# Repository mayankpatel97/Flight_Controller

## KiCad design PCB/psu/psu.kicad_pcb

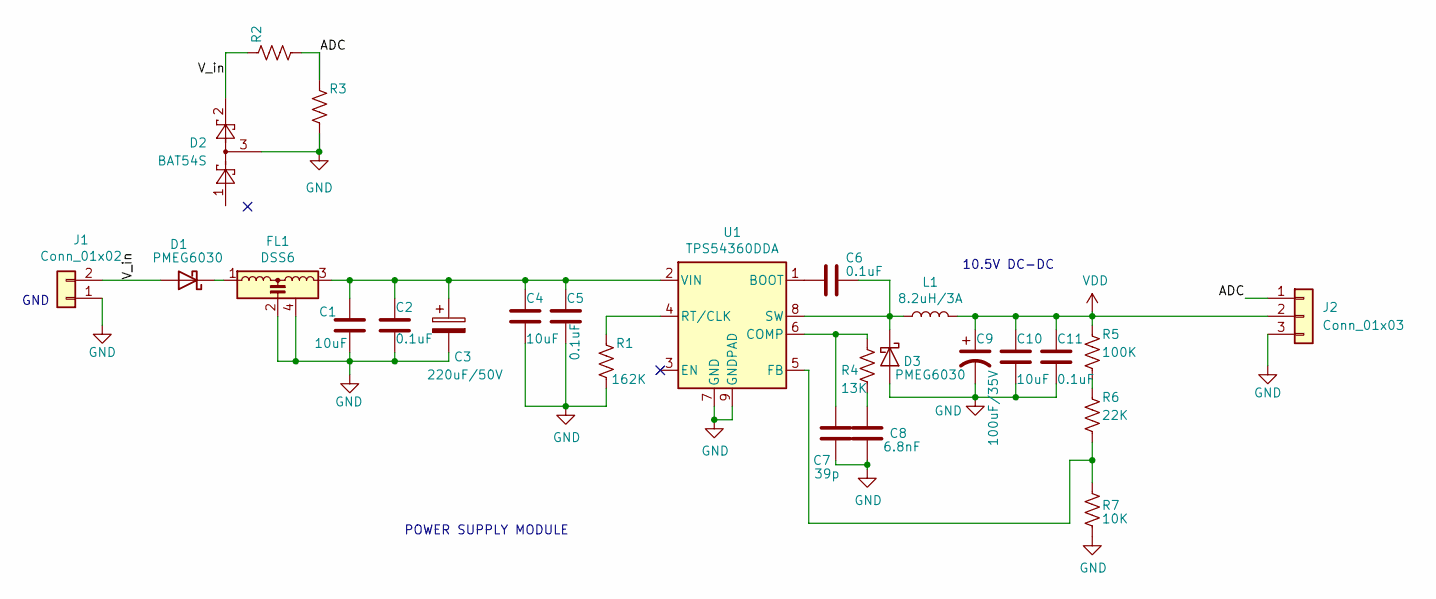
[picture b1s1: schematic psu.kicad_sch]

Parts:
C1, C4, C10: 10uF; C_0805_2012Metric_Pad1.18x1.45mm_HandSolder
C2, C5, C6, C11: 0.1uF; C_0805_2012Metric_Pad1.18x1.45mm_HandSolder
C3: 220uF/50V; CP_Elec_10x14.3
C7: 39p; C_0805_2012Metric_Pad1.18x1.45mm_HandSolder
C8: 6.8nF; C_0805_2012Metric_Pad1.18x1.45mm_HandSolder
C9: 100uF/35V; CP_Elec_10x14.3
D1, D3: PMEG6030; D_SMA
D2: BAT54S; SOT-23
FL1: DSS6; EMI_Filter_NFM41CC102R2A3L
J1: Conn_01x02; JST_XH_B2B-XH-A_1x02_P2.50mm_Vertical
J2: Conn_01x03; JST_EH_B3B-EH-A_1x03_P2.50mm_Vertical
L1: 8.2uH/3A; L_Neosid_Ms85
R1: 162K; R_0805_2012Metric_Pad1.20x1.40mm_HandSolder
R2, R3: 0; R_0805_2012Metric_Pad1.20x1.40mm_HandSolder
R4: 13K; R_0805_2012Metric_Pad1.20x1.40mm_HandSolder
R5: 100K; R_0805_2012Metric_Pad1.20x1.40mm_HandSolder
R6: 22K; R_0805_2012Metric_Pad1.20x1.40mm_HandSolder
R7: 10K; R_0805_2012Metric_Pad1.20x1.40mm_HandSolder
U1: TPS54360DDA; SOIC-8-1EP_3.9x4.9mm_P1.27mm_EP2.514x3.2mm_ThermalVias

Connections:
/ADC: J2.1, R2.2, R3.1
/V_in: D1.2 (A), D2.2, J1.2, R2.1
GND: C1.2, C2.2, C3.2, C4.2, C5.2, C7.1, C8.1, C9.2, C10.2, C11.2, D2.3, D3.2 (A), FL1.2, FL1.4 (GND), J1.1, J2.3, R1.2, R3.2, R7.2, U1.7 (GND), U1.9 (GNDPAD)
unnamed: C1.1, C2.1, C3.1, C4.1, C5.1, FL1.3, U1.2 (VIN)
unnamed: C6.1, D3.1 (K), L1.1, U1.8 (SW)
unnamed: C6.2, U1.1 (BOOT)
unnamed: C7.2, R4.1, U1.6 (COMP)
unnamed: C8.2, R4.2
unnamed: D1.1 (K), FL1.1
unnamed: R1.1, U1.4 (RT/CLK)
unnamed: R5.2, R6.1
unnamed: R6.2, R7.1, U1.5 (FB)
VDD: C9.1, C10.1, C11.1, J2.2, L1.2, R5.1

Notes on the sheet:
10.5V DC-DC
POWER SUPPLY MODULE
GND

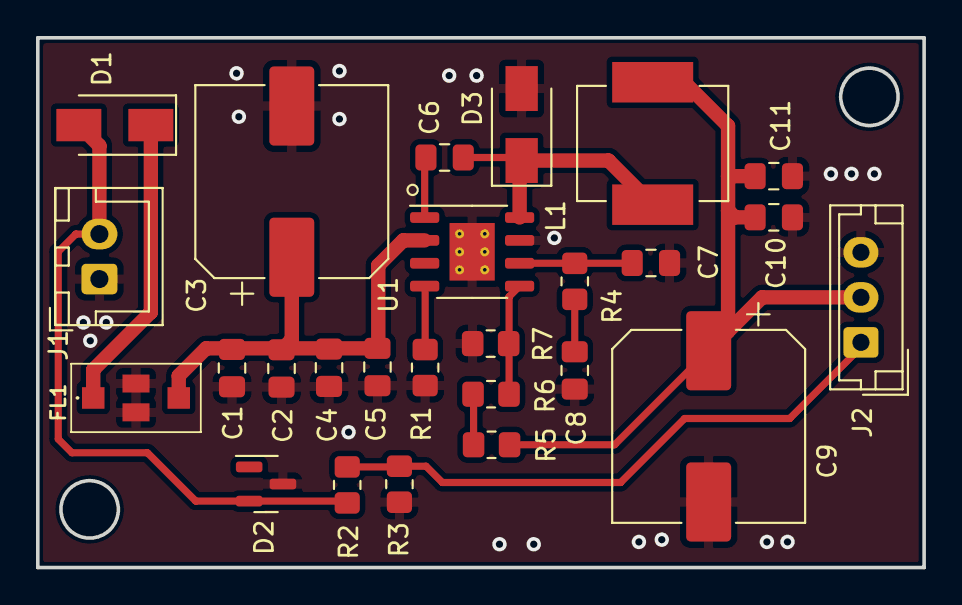
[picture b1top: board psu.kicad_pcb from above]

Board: 2 copper layers, 49.2 x 29.4 mm, 26 parts (0 on the bottom side), 13 nets.

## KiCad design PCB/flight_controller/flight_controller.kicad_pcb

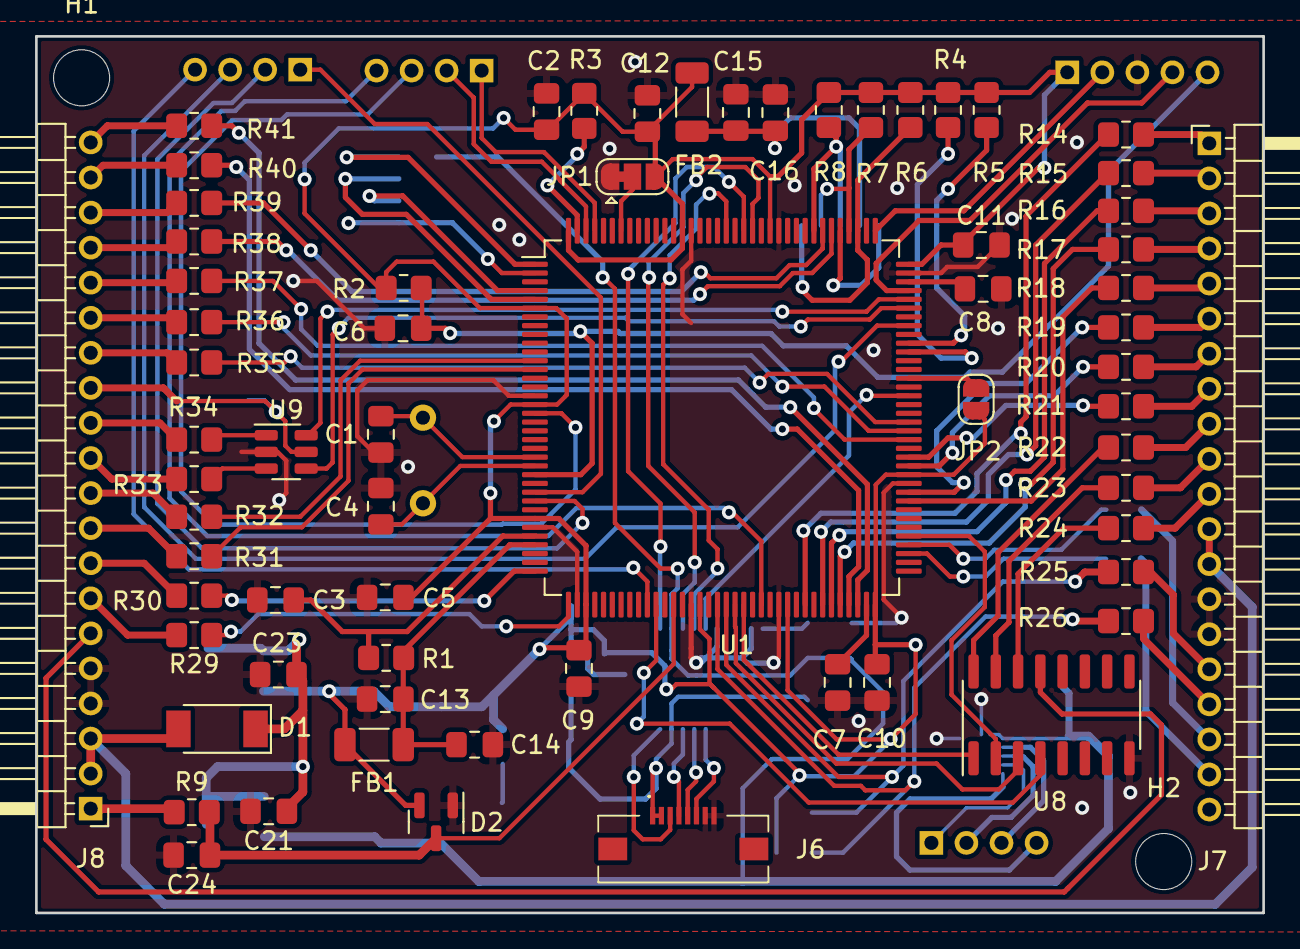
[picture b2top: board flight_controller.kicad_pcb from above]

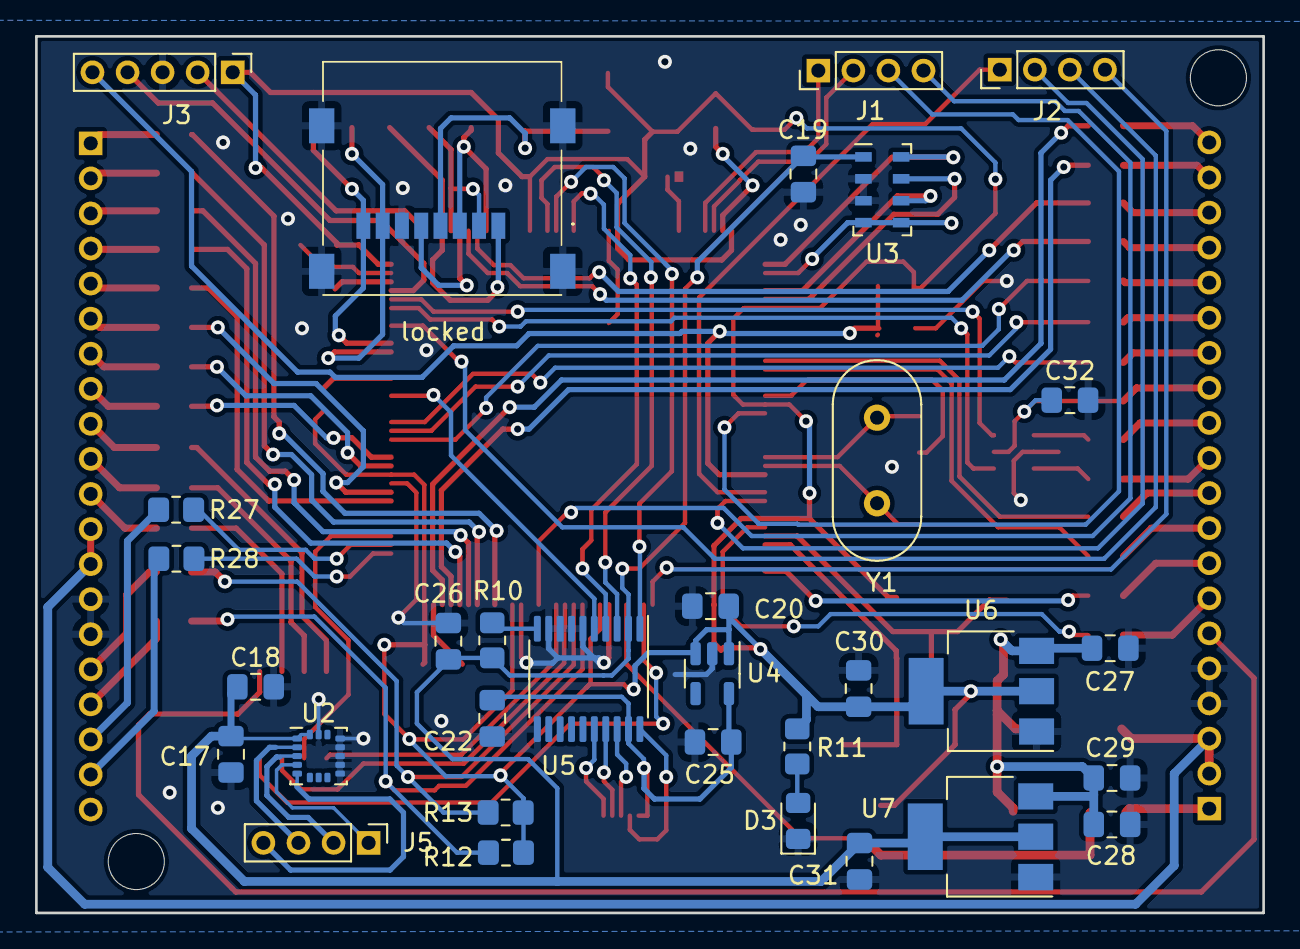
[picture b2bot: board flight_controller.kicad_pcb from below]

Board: 2 copper layers, 70.0 x 50.0 mm, 100 parts (32 on the bottom side), 117 nets.

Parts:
C1, C4: 27pF; C_0805_2012Metric_Pad1.18x1.45mm_HandSolder
C2, C5, C6, C9, C10, C11, C12, C13, C16, C17, C18, C19, C20, C22, C25, C26, C27, C29, C30, C31, C32: 0.1uF; C_0805_2012Metric_Pad1.18x1.45mm_HandSolder
C3, C7, C8, C14, C24: 1uF; C_0805_2012Metric_Pad1.18x1.45mm_HandSolder
C15, C21, C23: 22uF; C_0805_2012Metric_Pad1.18x1.45mm_HandSolder
C28: 10uF; C_0805_2012Metric_Pad1.18x1.45mm_HandSolder
D1: PMEG6030EP; D_SOD-128
D2: BAT54S; SOT-23
D3: LED; LED_0805_2012Metric_Pad1.15x1.40mm_HandSolder
FB1, FB2: FerriteBead; L_1206_3216Metric_Pad1.22x1.90mm_HandSolder
H1, H2: MH; MountingHole_3.2mm_M3
J1, J2, J5: Conn_01x04; PinHeader_1x04_P2.00mm_Vertical
J3: Conn_01x05; PinHeader_1x05_P2.00mm_Vertical
J6: Conn_01x08; 687108183722
J7, J8: Conn_01x20; PinHeader_1x20_P2.00mm_Horizontal
JP1: Jumper_3_Bridged12; SolderJumper-3_P1.3mm_Bridged12_RoundedPad1.0x1.5mm
JP2: Jumper_2_Open; SolderJumper-2_P1.3mm_Open_RoundedPad1.0x1.5mm
R1: 47R; R_0805_2012Metric_Pad1.20x1.40mm_HandSolder
R2, R3, R8, R10, R12, R13: 10K; R_0805_2012Metric_Pad1.20x1.40mm_HandSolder
R4, R5, R6, R7: 47K; R_0805_2012Metric_Pad1.20x1.40mm_HandSolder
R9: 100E; R_0805_2012Metric_Pad1.20x1.40mm_HandSolder
R11: 470R; R_0805_2012Metric_Pad1.20x1.40mm_HandSolder
R14, R15, R16, R17, R18, R19, R20, R21, R22, R23, R24, R25, R26, R27, R28, R29, R30, R31, R32, R35, R36, R37, R38, R39, R40, R41: 100R; R_0805_2012Metric_Pad1.20x1.40mm_HandSolder
R33, R34: 22R; R_0805_2012Metric_Pad1.20x1.40mm_HandSolder
U1: STM32H743ZITx; LQFP-144_20x20mm_P0.5mm
U2: ICM-20602; LGA-16_3x3mm_P0.5mm_LayoutBorder3x5y
U3: MS5611-01BA; LGA-8_3x5mm_P1.25mm
U4: NCP161ASN180T1G; SOT-23-5
U5: TXS0108EPW; TSSOP-20_4.4x6.5mm_P0.65mm
U6, U7: LD1117S33TR_SOT223; SOT-223-3_TabPin2
U8: ULN2003; SOIC-16_3.9x9.9mm_P1.27mm
U9: USBLC6-2SC6; SOT-23-6
Y1: 24Mhz; Crystal_HC49-4H_Vertical
locked: 5009010801; 5009010801_sd_molex

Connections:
+1V8: C22.1, C25.1, J6.1, J6.2, U4.5 (VOUT), U5.19 (VCCB)
+3.3VA: C17.1, C18.1, C19.1, C26.1, C31.1, R10.1, U2.1 (VDDIO), U2.16 (VDD), U3.1 (VDD), U5.2 (VCCA), U7.2 (VO)
+3V3: C2.1, C5.1, C9.1, C10.1, C11.1, C12.1, C20.1, C30.1, D2.2, FB1.2, FB2.1, J3.1, JP1.3 (B), JP2.1 (A), R2.1, R3.1, R4.2, R5.2, R6.2, R7.2, R8.2, R11.1, R12.2, R13.2, U1.6 (VBAT), U1.17 (VDD), U1.30 (VDD), U1.39 (VDD), U1.52 (VDD), U1.62 (VDD), U1.72 (VDD), U1.84 (VDD), U1.108 (VDD), U1.121 (VDD), U1.131 (VDD), U1.144 (VDD), U4.1 (VIN), U4.3 (ON/~OFF), U6.2 (VO)
+5V: C21.1, C23.1, C27.1, C28.1, C29.1, D1.1 (K), U6.3 (VI), U7.3 (VI)
/BAR_CSB: U1.2 (PE3), U3.4 (CSB), U3.5 (CSB)
/BAR_SCK: U1.1 (PE2), U3.8 (SCLK)
/BAR_SDI: U1.5 (PE6), U3.7 (SDI/SDA)
/BAR_SDO: U1.4 (PE5), U3.6 (SDO)
/BUZZER: U1.47 (PB1), U8.4 (I4)
/B_LED: U1.56 (PG0), U8.3 (I3)
/CAN1_RX: R38.1, U1.114 (PD0)
/CAN1_TX: R39.1, U1.115 (PD1)
/ECO: R28.1, U1.75 (PB14)
/ESC1: R14.1, U1.64 (PE11)
/ESC2: R15.1, U1.66 (PE13)
/ESC3: R16.1, U1.67 (PE14)
/ESC4: R17.1, U1.68 (PE15)
/ESC5: R18.1, U1.81 (PD12)
/ESC6: R19.1, U1.82 (PD13)
/ESC7: R20.1, U1.85 (PD14)
/ESC8: R21.1, U1.86 (PD15)
/FLOW_METER1: R36.1, U1.89 (PG4)
/GPS_RX: R29.1, U1.37 (PA3)
/GPS_TX: R30.1, U1.36 (PA2)
/G_LED: U1.77 (PD8), U8.2 (I2)
/IMU_CS: U1.93 (PG8), U5.5 (A4)
/IMU_SCL: U1.126 (PG11), U5.4 (A3)
/IMU_SDI: U1.123 (PD7), U5.3 (A2)
/IMU_SDO: U1.124 (PG9), U5.1 (A1)
/IO/5V_IN: D1.2 (A), J7.12, J7.13, J8.2, J8.3
/IO/BAT: J8.1, R9.1
/IO/BUZZERn: J8.6, U8.13 (O4)
/IO/B_LEDn: R24.1, U8.14 (O3)
/IO/G_LEDn: R23.1, U8.15 (O2)
/IO/R_LEDn: R22.1, U8.16 (O1)
/IO/USB_DM_IN: R33.1, U9.3 (I/O2)
/IO/USB_DP_IN: R34.1, U9.1 (I/O1)
/IO/USB_VCC: C32.1, J8.13, U9.5 (VBUS)
/MAVLINK_RX: R40.1, U1.69 (PB10)
/MAVLINK_TX: R41.1, U1.70 (PB11)
/MCU/GPIO_PB0: J2.4, U1.46 (PB0)
/MCU/NRST: C6.1, J3.5, R2.2, U1.25 (NRST)
/MCU/SDMMC1_CLK: U1.113 (PC12), locked.5
/MCU/SDMMC1_CMD: R8.1, U1.116 (PD2), locked.3
/MCU/SDMMC1_D0: R4.1, U1.98 (PC8), locked.7
/MCU/SDMMC1_D1: R5.1, U1.99 (PC9), locked.8
/MCU/SDMMC1_D2: R6.1, U1.111 (PC10), locked.1
/MCU/SDMMC1_D3: R7.1, U1.112 (PC11), locked.2
/MCU/SPI2_MISO: J2.2, U1.28 (PC2_C)
/MCU/SPI2_MOSI: J2.1, U1.27 (PC1)
/MCU/SPI2_SCK: J2.3, U1.101 (PA9)
/MCU/SWD_SWCLK: J3.2, U1.109 (PA14)
/MCU/SWD_SWDIO: J3.4, U1.105 (PA13)
/MCU/UART7_RX: J1.3, U1.18 (PF6)
/MCU/UART7_TX: J1.4, U1.59 (PE8)
/MCU/UART8_RX: J1.1, U1.141 (PE0)
/MCU/UART8_TX: J1.2, U1.142 (PE1)
/MCU/VDDA: C13.1, C14.1, FB1.1, R1.1, U1.33 (VDDA)
/R_LED: U1.57 (PG1), U8.1 (I1)
/SCL: R13.1, R25.1, U1.55 (PF15)
/SDA: R12.1, R26.1, U1.54 (PF14)
/SPARE_IO1: R37.1, U1.88 (PG3)
/SWITCH1: R31.1, U1.13 (PF3)
/SWITCH2: R32.1, U1.12 (PF2)
/Sensors/IMU_CS: J5.4, U2.5 (~CS)
/Sensors/IMU_SCL: J5.3, U2.2 (SCL/SPC)
/Sensors/IMU_SDI: J5.2, U2.3 (SDA/SDI)
/Sensors/IMU_SDO: J5.1, U2.4 (SAO/SD0)
/TRIGGER: R27.1, U1.76 (PB15)
/USB_DM: U1.103 (PA11), U9.4 (I/O2)
/USB_DP: U1.104 (PA12), U9.6 (I/O1)
/VBAT: C24.1, D2.3, R9.2, U1.49 (PF11)
/WATER_PUMP1: R35.1, U1.90 (PG5)
GND: C1.2, C2.2, C3.2, C4.2, C5.2, C6.2, C7.2, C8.2, C9.2, C10.2, C11.2, C12.2, C13.2, C14.2, C15.2, C16.2, C17.2, C18.2, C19.2, C20.2, C21.2, C22.2, C23.2, C24.2, C25.2, C26.2, C27.2, C28.2, C29.2, C30.2, C31.2, C32.2, D2.1, D3.1 (K), J3.3, J6.7, J6.8, J7.14, J7.15, J8.4, J8.5, JP1.1 (A), U1.16 (VSS), U1.31 (VSSA), U1.38 (VSS), U1.51 (VSS), U1.61 (VSS), U1.83 (VSS), U1.94 (VSS), U1.107 (VSS), U1.120 (VSS), U1.130 (VSS), U2.9 (GND), U2.10 (GND), U2.11 (GND), U2.12 (GND), U2.13 (GND), U2.15 (GND), U3.2 (PS), U3.3 (GND), U4.2 (GND), U5.6 (A5), U5.7 (A6), U5.8 (A7), U5.9 (A8), U5.11 (GND), U6.1 (GND), U7.1 (GND), U8.8 (GND), U9.2 (GND), locked.6, locked.MP1, locked.MP2, locked.MP3, locked.MP4
unnamed: C15.1, C16.1, FB2.2, locked.4
unnamed: D3.2 (A), R11.2
unnamed: J6.3, U5.20 (B1)
unnamed: J6.4, U5.18 (B2)
unnamed: J6.5, U5.17 (B3)
unnamed: J6.6, U5.16 (B4)
unnamed: J7.1, R14.2
unnamed: J7.2, R15.2
unnamed: J7.3, R16.2
unnamed: J7.4, R17.2
unnamed: J7.5, R18.2
unnamed: J7.6, R19.2
unnamed: J7.7, R20.2
unnamed: J7.8, R21.2
unnamed: J7.9, R22.2
unnamed: J7.10, R23.2
unnamed: J7.11, R24.2
unnamed: J7.16, R25.2
unnamed: J7.17, R26.2
unnamed: J7.18, R27.2
unnamed: J7.19, R28.2
unnamed: J8.7, R29.2
unnamed: J8.8, R30.2
unnamed: J8.9, R31.2
unnamed: J8.10, R32.2
unnamed: J8.11, R33.2
unnamed: J8.12, R34.2
unnamed: J8.14, R35.2
unnamed: J8.15, R36.2
unnamed: J8.16, R37.2
unnamed: J8.17, R38.2
unnamed: J8.18, R39.2
unnamed: J8.19, R40.2
unnamed: J8.20, R41.2
unnamed: JP1.2 (C), U1.138 (BOOT0)
unnamed: JP2.2 (B), U1.95 (VDD33_USB)
unnamed: R3.2, U1.143 (PDR_ON)
unnamed: C1.1, U1.23 (PH0), Y1.1
unnamed: C4.1, U1.24 (PH1), Y1.2
unnamed: C7.1, U1.71 (VCAP1)
unnamed: C8.1, U1.106 (VCAP2)
unnamed: C3.1, R1.2, U1.32 (VREF+)
unnamed: R10.2, U5.10 (OE)

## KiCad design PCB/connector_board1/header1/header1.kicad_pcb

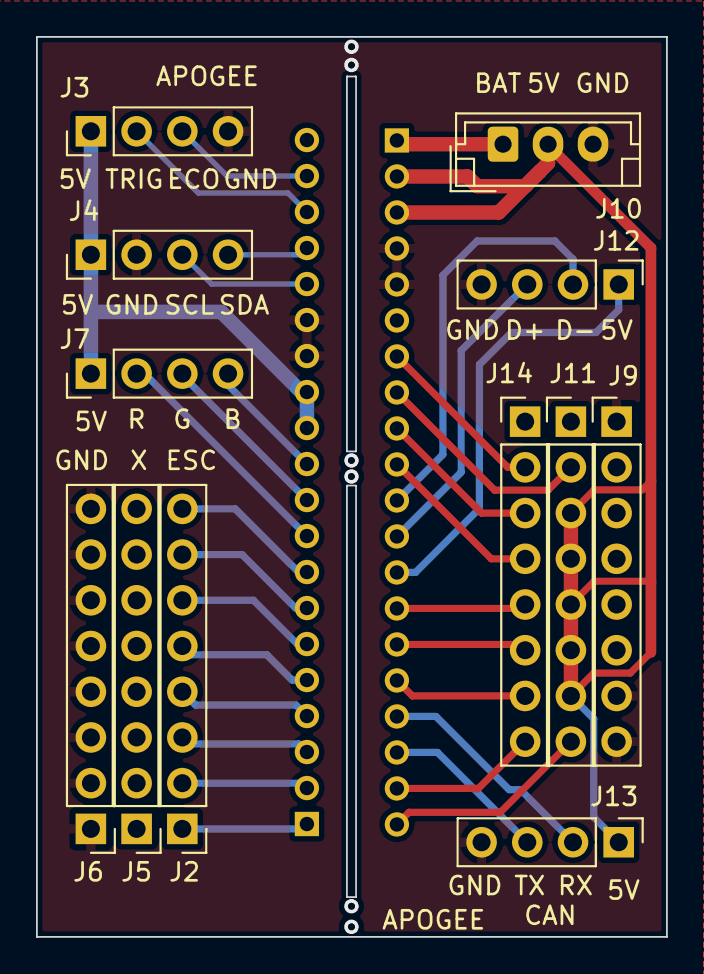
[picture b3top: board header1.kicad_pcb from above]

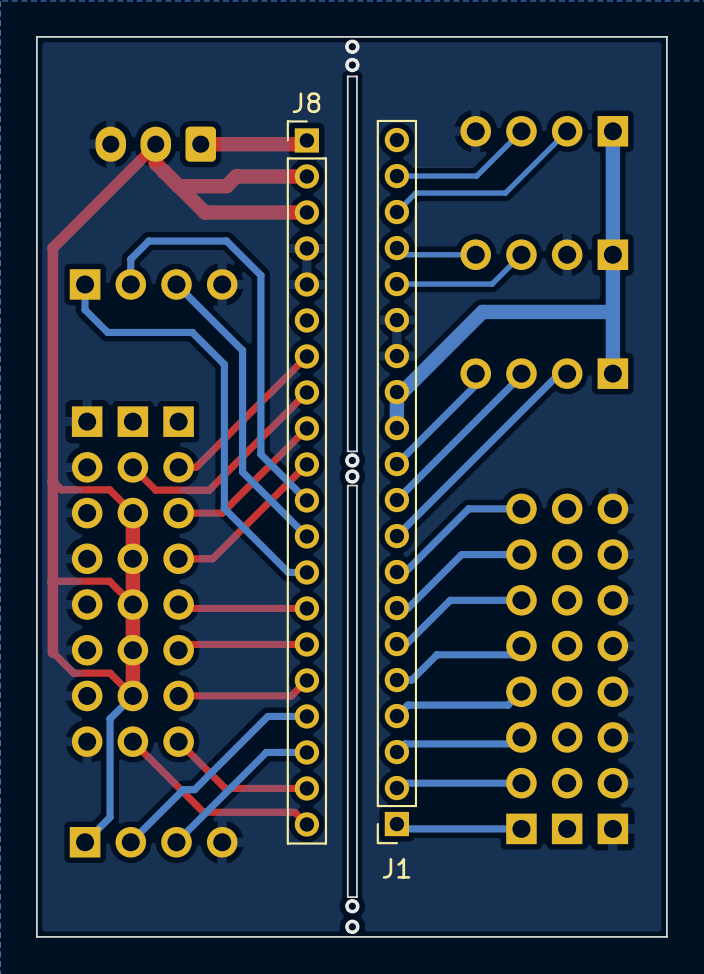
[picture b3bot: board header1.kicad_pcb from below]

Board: 2 copper layers, 35.0 x 50.0 mm, 14 parts (2 on the bottom side), 33 nets.

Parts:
J1: Conn_01x20; PinSocket_1x20_P2.00mm_Vertical
J2, J5, J6, J9, J11, J14: Conn_01x08; PinHeader_1x08_P2.54mm_Vertical
J3, J4, J7, J12, J13: Conn_01x04; PinHeader_1x04_P2.54mm_Vertical
J8: Conn_01x20; PinHeader_1x20_P2.00mm_Vertical
J10: Conn_01x03; JST_EH_B3B-EH-A_1x03_P2.50mm_Vertical

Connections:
/5V: J8.2, J8.3, J10.2, J11.3, J11.4, J11.5, J11.6, J11.7, J13.1
/5VA: J1.12, J1.13, J3.1, J4.1, J7.1
/BAT: J8.1, J10.1
/B_LEDn: J1.11, J7.4
/CAN1_RX: J8.17, J13.2
/CAN1_TX: J8.18, J13.3
/ECO: J1.19, J3.3
/ESC1: J1.1, J2.1
/ESC2: J1.2, J2.2
/ESC3: J1.3, J2.3
/ESC4: J1.4, J2.4
/ESC5: J1.5, J2.5
/ESC6: J1.6, J2.6
/ESC7: J1.7, J2.7
/ESC8: J1.8, J2.8
/FLOW_METER: J8.15, J14.6
/GPS_RX: J8.7, J14.2
/GPS_TX: J8.8, J11.2
/G_LEDn: J1.10, J7.3
/MAVLINK_RX: J8.19, J14.8
/MAVLINK_TX: J8.20, J11.8
/R_LEDn: J1.9, J7.2
/SCL: J1.16, J4.3
/SDA: J1.17, J4.4
/SPARE_IO1: J8.16, J14.7
/SWITCH1: J8.9, J14.3
/SWITCH2: J8.10, J14.4
/TRIGGER: J1.18, J3.2
/USB_DM: J8.11, J12.2
/USB_DP: J8.12, J12.3
/USB_VCC: J8.13, J12.1
/WATER_PUMP: J8.14, J14.5
GND: J1.14, J1.15, J3.4, J4.2, J6.1, J6.2, J6.3, J6.4, J6.5, J6.6, J6.7, J6.8, J8.4, J8.5, J9.1, J9.2, J9.3, J9.4, J9.5, J9.6, J9.7, J9.8, J10.3, J12.4, J13.4

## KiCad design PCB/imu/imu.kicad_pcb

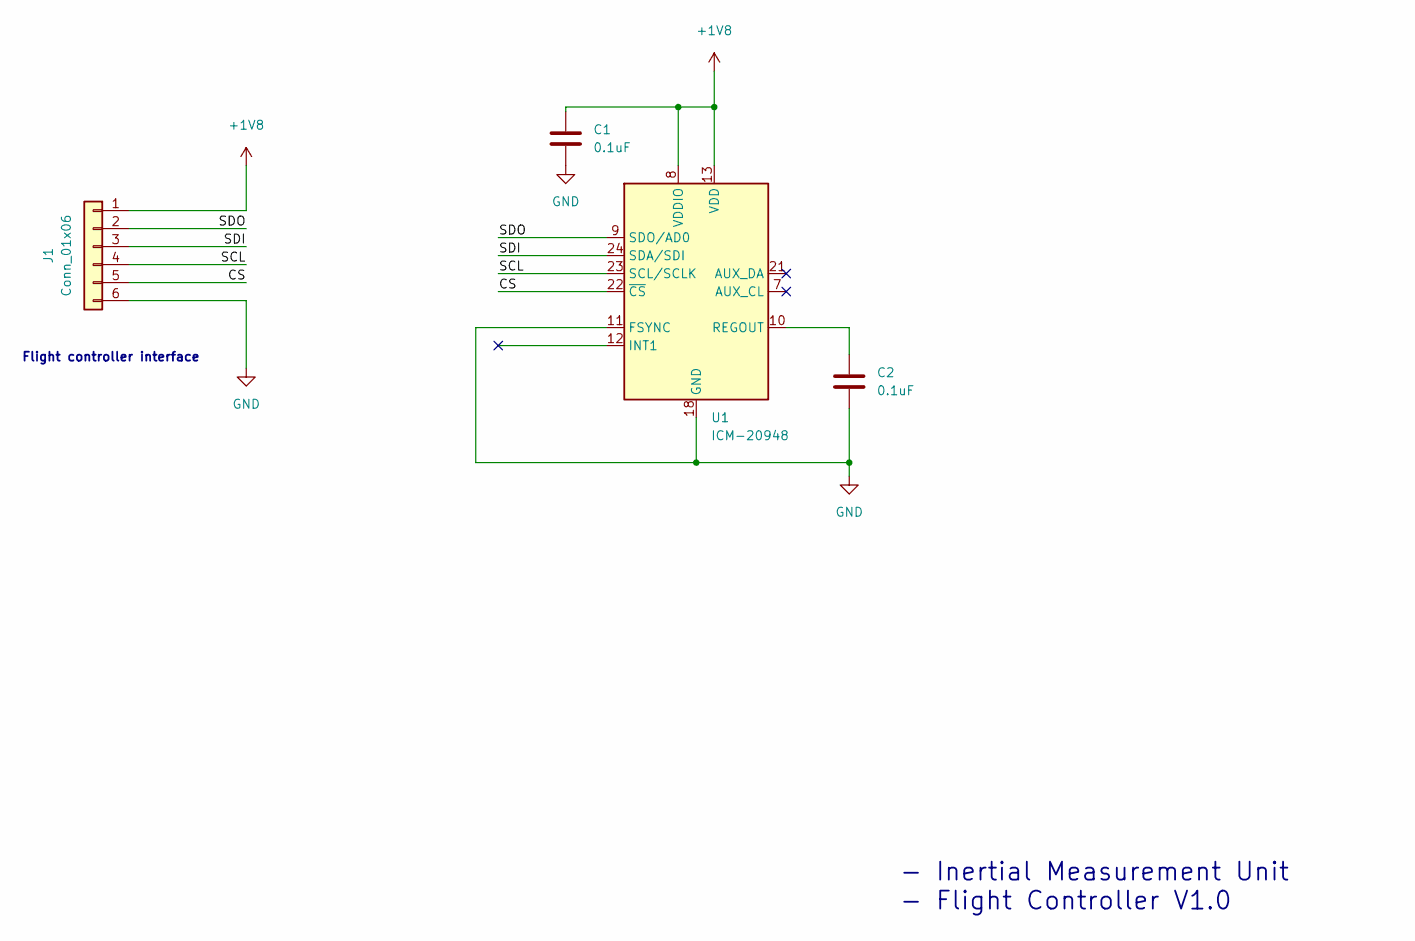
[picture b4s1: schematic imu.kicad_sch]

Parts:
C1, C2: 0.1uF; C_0603_1608Metric
J1: Conn_01x06; 687108183722
U1: ICM-20948; InvenSense_QFN-24_3x3mm_P0.4mm

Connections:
+1V8: C1.1, J1.1, U1.8 (VDDIO), U1.13 (VDD)
/CS: J1.5, U1.22 (~CS)
/SCL: J1.4, U1.23 (SCL/SCLK)
/SDI: J1.3, U1.24 (SDA/SDI)
/SDO: J1.2, U1.9 (SDO/AD0)
GND: C1.2, C2.2, J1.6, U1.11 (FSYNC), U1.18 (GND), U1.20 (GND)
unnamed: C2.1, U1.10 (REGOUT)

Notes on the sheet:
Flight controller interface
- Inertial Measurement Unit - Flight Controller V1.0

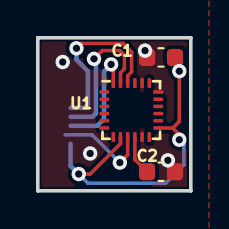
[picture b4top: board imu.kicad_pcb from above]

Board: 2 copper layers, 8.5 x 8.5 mm, 4 parts (1 on the bottom side), 7 nets.
